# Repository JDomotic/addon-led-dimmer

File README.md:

# 9 Channel PWM Dimmer Addon
This is a custom made PWM dimmer addon which fits on the back of the [Wireless sensor board](https://github.com/JDomotic/esp12-wireless-sensor-board) .

The board can receive commands over uart with configurable transition speed per channel

## Version 1 | 05-01-2019
**Features**:
* Onboard 500ma 3.3v power regulator to power itself and the wireless sensor board
* Support for 12v led strips 
* 9 PWM channels 8 bit

**Schematic**

**BOM**

**Ref**|**Qnty**|**Value**|**Footprint**|**Vendor (LCSC)**
:-----: | :-----: | :-----: | :-----: | :-----:
C1,|1|680uF|Capacitor\_THT:CP\_Radial\_D8.0mm\_P3.50mm|C59427|$0,0906
C2,|1|120uF|Capacitor\_THT:CP\_Radial\_D6.3mm\_P2.50mm|C251018|$0,1182
C7,|1|0.1uf|Capacitor\_SMD:C\_1206\_3216Metric\_Pad1.42x1.75mm\_HandSolder|C128353|$0,0179
D1,|1|1N5817|Diode\_THT:D\_DO-41\_SOD81\_P10.16mm\_Horizontal|C169165|$0,0223
J1,|1|RGB\_VIN|TerminalBlock\_Phoenix:TerminalBlock\_Phoenix\_MKDS-1,5-2\_1x02\_P5.00mm\_Horizontal|C8269|$0,0954
J3,|1|Conn\_01x05\_Male RIGHT|Connector\_PinHeader\_2.54mm:PinHeader\_1x05\_P2.54mm\_Vertical|-|0
J4,|1|Conn\_01x05\_Male|Connector\_PinHeader\_2.54mm:PinHeader\_1x05\_P2.54mm\_Vertical|-|0
J5,|2|RGB\_strip\_3|TerminalBlock\_Phoenix:TerminalBlock\_Phoenix\_MKDS-1,5-4\_1x04\_P5.00mm\_Horizontal|C8269|$0,1908
J6,|2|RGB\_strip\_1|TerminalBlock\_Phoenix:TerminalBlock\_Phoenix\_MKDS-1,5-4\_1x04\_P5.00mm\_Horizontal|C8269|$0,1908
J9,|2|RGB\_strip\_2|TerminalBlock\_Phoenix:TerminalBlock\_Phoenix\_MKDS-1,5-4\_1x04\_P5.00mm\_Horizontal|C8269|$0,1908
L1,|1|100uH|Inductor\_SMD:L\_6.3x6.3\_H3|C10122|$0,0731
Q1, Q2, Q3, Q4, Q5, Q6, Q10, Q11, Q12,|9|PMV16XNR|Package\_TO\_SOT\_SMD:SOT-23|C110920|$0,8064
R1,|1|10K|Resistor\_SMD:R\_0805\_2012Metric\_Pad1.15x1.40mm\_HandSolder|C103904|$0,0025
R2, R3, R4, R5, R6, R7, R8, R9, R10,|9|1K|Resistor\_SMD:R\_0805\_2012Metric\_Pad1.15x1.40mm\_HandSolder|C95781|$0,0360
U1,|1|ATTINY414|Package\_SO:SOIC-14\_3.9x8.7mm\_P1.27mm|C189365|$0,7137
U2,|1|LM2594M-3.3|Package\_SO:SOIC-8\_3.9x4.9mm\_P1.27mm|C316691|$0,6088

**Render**

**Assembled**

**Issues**

As vissible in the assembly, there are a few issues. 
1. The wrong SOT-23 footprint is used. Due this, the mosfets needs to be soldered upside down (This because pin 1 and 2 are flipped) 
2. The wrong pin layout for U2 is used. The trace to pad 1, 2 and 4 needs to be scratched. Pad 4 needs to be connected to D1, pad 8 to 3.3v and pad 7 to VIN.

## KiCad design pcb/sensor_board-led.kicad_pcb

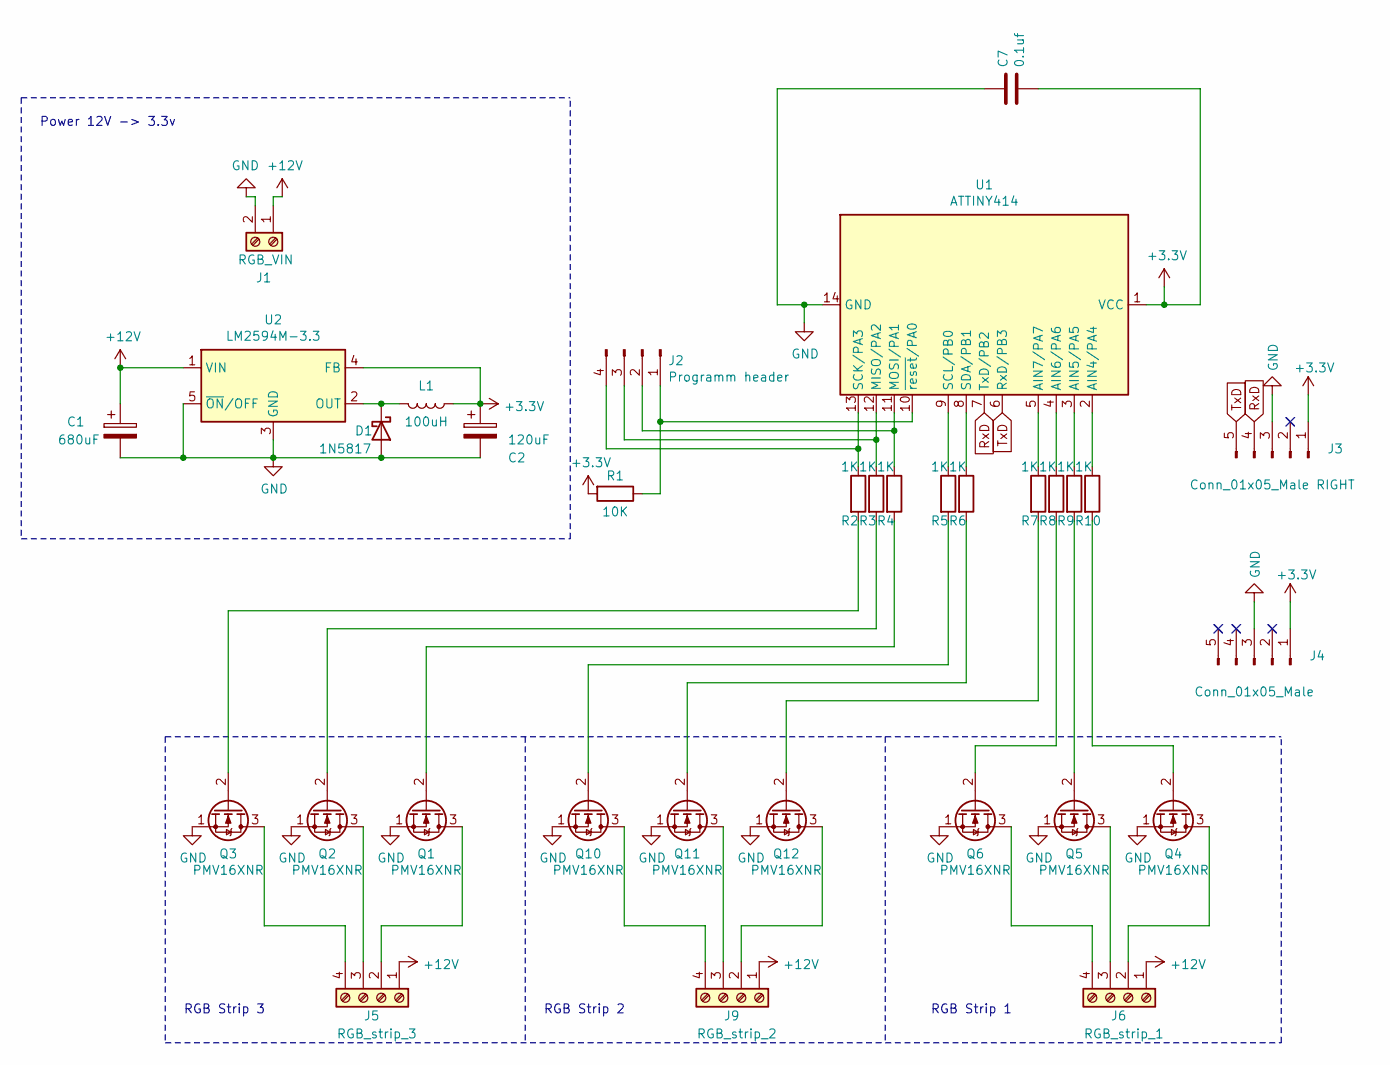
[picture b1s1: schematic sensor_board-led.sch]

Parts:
C1: 680uF; CP_Radial_D8.0mm_P3.50mm
C2: 120uF; CP_Radial_D6.3mm_P2.50mm
C7: 0.1uf; C_1206_3216Metric_Pad1.42x1.75mm_HandSolder
D1: 1N5817; D_DO-41_SOD81_P10.16mm_Horizontal
J1: RGB_VIN; TerminalBlock_Phoenix_MKDS-1,5-2_1x02_P5.00mm_Horizontal
J2: Programm header; PinHeader_1x04_P2.54mm_Vertical_SMD_Pin1Left
J3: Conn_01x05_Male RIGHT; PinHeader_1x05_P2.54mm_Vertical
J4: Conn_01x05_Male; PinHeader_1x05_P2.54mm_Vertical
J5: RGB_strip_3; TerminalBlock_Phoenix_MKDS-1,5-4_1x04_P5.00mm_Horizontal
J6: RGB_strip_1; TerminalBlock_Phoenix_MKDS-1,5-4_1x04_P5.00mm_Horizontal
J9: RGB_strip_2; TerminalBlock_Phoenix_MKDS-1,5-4_1x04_P5.00mm_Horizontal
L1: 100uH; L_6.3x6.3_H3
Q1, Q2, Q3, Q4, Q5, Q6, Q10, Q11, Q12: PMV16XNR; SOT-23
R1: 10K; R_0805_2012Metric_Pad1.15x1.40mm_HandSolder
R2, R3, R4, R5, R6, R7, R8, R9, R10: 1K; R_0805_2012Metric_Pad1.15x1.40mm_HandSolder
U1: ATTINY414; SOIC-14_3.9x8.7mm_P1.27mm
U2: LM2594M-3.3; SOIC-8_3.9x4.9mm_P1.27mm

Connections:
+3V3: C2.1, C7.2, J3.1, J4.1, L1.1, R1.2, U1.1 (VCC), U2.4 (FB)
+12V: C1.1, J1.1, J5.1, J6.1, J9.1, U2.1 (VIN)
GND: C1.2, C2.2, C7.1, D1.2 (A), J1.2, J3.3, J4.3, Q1.1 (S), Q2.1 (S), Q3.1 (S), Q4.1 (S), Q5.1 (S), Q6.1 (S), Q10.1 (S), Q11.1 (S), Q12.1 (S), U1.14 (GND), U2.3 (GND), U2.5 (~ON~/OFF)
unnamed: D1.1 (K), L1.2, U2.2 (OUT)
unnamed: J2.1, R1.1, U1.10 (~reset~/PA0)
unnamed: J2.2, R4.1, U1.11 (MOSI/PA1)
unnamed: J2.3, R3.1, U1.12 (MISO/PA2)
unnamed: J2.4, R2.1, U1.13 (SCK/PA3)
unnamed: J5.2, Q1.3 (D)
unnamed: J5.3, Q2.3 (D)
unnamed: J5.4, Q3.3 (D)
unnamed: J6.2, Q4.3 (D)
unnamed: J6.3, Q5.3 (D)
unnamed: J6.4, Q6.3 (D)
unnamed: J9.2, Q12.3 (D)
unnamed: J9.3, Q11.3 (D)
unnamed: J9.4, Q10.3 (D)
unnamed: Q1.2 (G), R4.2
unnamed: Q2.2 (G), R3.2
unnamed: Q3.2 (G), R2.2
unnamed: Q4.2 (G), R10.2
unnamed: Q5.2 (G), R9.2
unnamed: Q6.2 (G), R8.2
unnamed: Q10.2 (G), R5.2
unnamed: Q11.2 (G), R6.2
unnamed: Q12.2 (G), R7.2
unnamed: R5.1, U1.9 (SCL/PB0)
unnamed: R6.1, U1.8 (SDA/PB1)
unnamed: R7.1, U1.5 (AIN7/PA7)
unnamed: R8.1, U1.4 (AIN6/PA6)
unnamed: R9.1, U1.3 (AIN5/PA5)
unnamed: R10.1, U1.2 (AIN4/PA4)
RxD: J3.4, U1.7 (TxD/PB2)
TxD: J3.5, U1.6 (RxD/PB3)

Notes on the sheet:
Power 12V -> 3.3v
RGB Strip 1
RGB Strip 3
RGB Strip 2

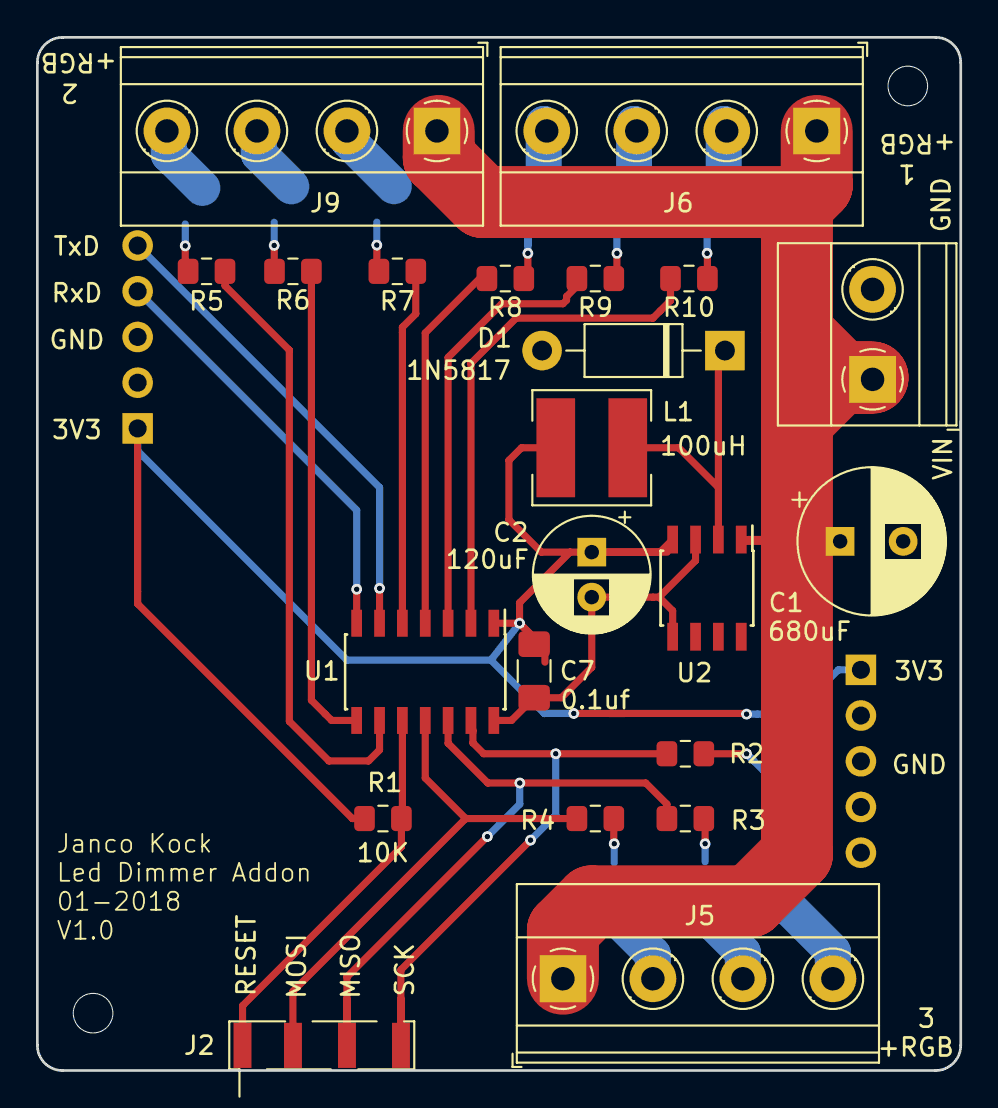
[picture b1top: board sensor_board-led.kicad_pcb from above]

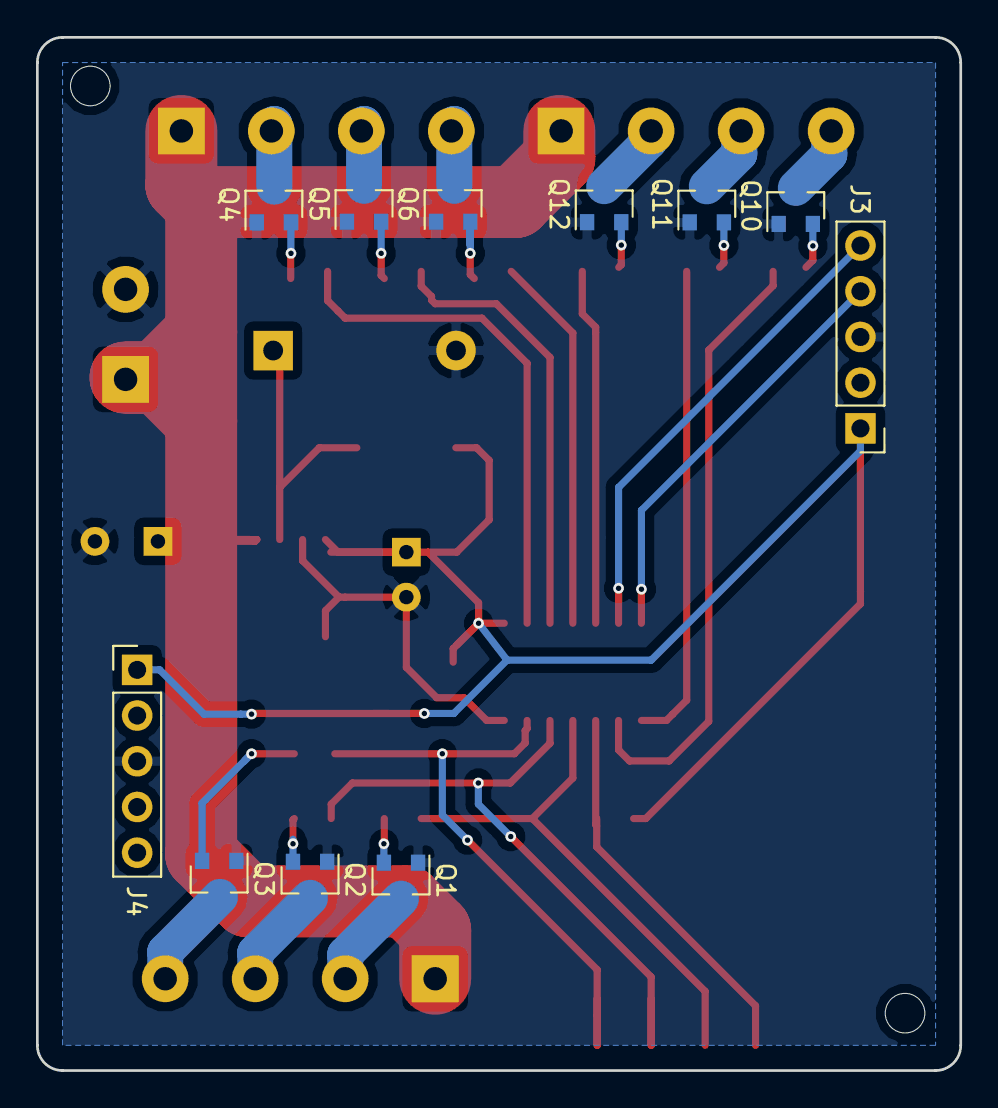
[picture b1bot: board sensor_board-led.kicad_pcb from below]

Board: 2 copper layers, 51.3 x 57.4 mm, 34 parts (11 on the bottom side), 34 nets.

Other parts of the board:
wREF**: MountingHole_2.2mm_M2_DIN965

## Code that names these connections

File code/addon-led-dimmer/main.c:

/*
 * main.c
 *
 * Created: 20-1-2019 15:04:12
 * Author : Janco Kock
 */				
#define F_CPU 10000000UL
#define BAUD_RATE 115200
#define USART0_BAUD_RATE ((float)F_CPU * 64) / (16 * (float)BAUD_RATE)

#define LED_OUTPUT_SCALE 10000UL

#define IDENTIFIER 'O'

#include <avr/io.h>
#include <avr/interrupt.h>
#include <stdbool.h>
#include <string.h>
#include <stdio.h>

// UART methods
int8_t USART_init();
uint8_t USART_read();
void USART_write(const uint8_t data);
void printString(const char myString[]);

const uint8_t gamme8[256] = {
	128, 128, 128, 128, 128, 128, 128, 128, 128, 128, 128, 128, 128, 128, 128, 128, 128, 128, 128, 128,
	129, 129, 129, 129, 129, 129, 129, 129, 129, 129, 129, 129, 129, 129, 129, 129, 129, 129, 129, 129,
	130, 130, 130, 130, 130, 130, 130, 130, 130, 130, 130, 130, 130, 130, 130, 130, 130, 130, 130, 130,
	131, 131, 131, 131, 131, 131, 131, 131, 131, 131, 131, 131, 131, 131, 131, 131, 131, 131, 131, 131,
	132, 132, 132, 132, 132, 132, 132, 132, 132, 132, 132, 132, 132, 132, 132, 132, 132, 132, 132, 132,
	133, 133, 133, 133, 133, 133, 133, 133, 133, 133, 134, 134, 134, 134, 134, 134, 134, 134, 134, 134,
	135, 135, 135, 135, 135, 135, 135, 135, 135, 135, 136, 136, 136, 136, 136, 136, 136, 136, 136, 136,
	137, 137, 137, 137, 137, 137, 137, 137, 137, 137, 138, 138, 138, 138, 138, 138, 138, 138, 138, 138,
	139, 139, 139, 139, 139, 139, 140, 140, 140, 140, 140, 140, 141, 141, 141, 141, 141, 141, 141, 141,
	142, 142, 142, 142, 143, 143, 143, 143, 143, 144, 144, 144, 144, 144, 145, 145, 145, 145, 145, 145,
	146, 146, 146, 147, 147, 147, 148, 148, 148, 149, 149, 149, 150, 150, 150, 151, 151, 151, 152, 152,
	152, 153, 153, 153, 154, 154, 154, 155, 155, 155, 156, 156, 156, 157, 157, 158, 158, 159, 159, 160,
	160, 161, 162, 163, 164, 165, 166, 167, 168, 169, 170, 171, 172, 173, 174, 175
};

typedef struct tick_value {uint8_t tick; uint8_t LEDS_PORTA; uint8_t LEDS_PORTB;} tick_value;
tick_value port_output_values_0[10] = {0};
tick_value port_output_values_1[10] = {0};
tick_value *port_output_values = port_output_values_0;
uint8_t current_port_values = 0;

uint8_t port_output_value_index = 0;
uint8_t current_tick = 0;

uint8_t wanted_led_output_values[18];
long led_output_values[9] = {0};
	
uint8_t uart_led_channel = 0;
bool recalculate_port_output_values = false;

///
/// Timer A for software PWM
///
ISR(TCA0_OVF_vect){
	current_tick++;

	//Set top based on gamma correction 
	TCA0_SINGLE_PER = gamme8[current_tick];
	
	if(current_tick == 0){
		port_output_value_index = 0;
		// Set correct output buffer
		if(current_port_values == 0){
			port_output_values = port_output_values_0;
		}else{
			port_output_values = port_output_values_1;
		}
	}
	
	if(current_tick == port_output_values[port_output_value_index].tick){
		PORTA_OUT = port_output_values[port_output_value_index].LEDS_PORTA; 
		PORTB_OUT = port_output_values[port_output_value_index].LEDS_PORTB;
		++port_output_value_index; 
	}

	// Clear interrupt flag
	TCA0_SINGLE_INTFLAGS = 0b00000001; 
} 

///
/// Timer B for UART package timeout check
///
ISR(TCB0_INT_vect){
	// Timeout between UART package occurs. Reset channel
	uart_led_channel = 0;
	// Disable
	TCB0_CTRLA = 0b00000010;
	// Clear interrupt flag
	TCB0_INTFLAGS = 0b00000001;
	// Write 'out of sync' package
	USART_write(IDENTIFIER);
}

///
/// UART methods
///
ISR(USART0_RXC_vect){
	wanted_led_output_values[uart_led_channel] =  USART0.RXDATAL;
	
	// Update package is done, so reset the UART package channel to 0
	if(uart_led_channel == 17){
		uart_led_channel = 0;
		
		recalculate_port_output_values = true;
		
		// Disable package timeout timer
		TCB0.CNT = 0;
		TCB0_CTRLA = 0b00000010;
	} else{
		uart_led_channel++;
		
		// Enable package timeout timer.
		TCB0.CNT = 0;
		TCB0_CTRLA = 0b00000011;
	}
}

int8_t USART_init(){
	int8_t sigrow_val = SIGROW.OSC20ERR3V; // read signed error
	int32_t baud_reg_val = USART0_BAUD_RATE;
	baud_reg_val *= (1024 + sigrow_val); // sum resolution + error
	baud_reg_val /= 1024; // divide by resolution
	USART0.BAUD = (int16_t) baud_reg_val;
	
	// Enable receive interrupt 
	USART0.CTRLA = 0b10000000;
  
	USART0.CTRLB = 0 << USART_MPCM_bp       /* Multi-processor Communication Mode: disabled */
	| 0 << USART_ODME_bp     /* Open Drain Mode Enable: disabled */
	| 1 << USART_RXEN_bp     /* Receiver enable: enabled */
	| USART_RXMODE_NORMAL_gc /* Normal mode */
	| 0 << USART_SFDEN_bp    /* Start Frame Detection Enable: disabled */
	| 1 << USART_TXEN_bp;    /* Transmitter Enable: enabled */

	USART0.CTRLC = USART_CMODE_ASYNCHRONOUS_gc /* Asynchronous Mode */
	| USART_CHSIZE_8BIT_gc /* Character size: 8 bit */
	| USART_PMODE_DISABLED_gc /* No Parity */
	| USART_SBMODE_1BIT_gc; /* 1 stop bit */

	return 0;
}

uint8_t USART_read()
{
	while (!(USART0.STATUS & USART_RXCIF_bm));
	return USART0.RXDATAL;
}

void USART_write(const uint8_t data)
{
	while (!(USART0.STATUS & USART_DREIF_bm));
	USART0.TXDATAL = data;
}

void printString(const char myString[]) {
	uint8_t i = 0;
	while (myString[i]) {
		USART_write(myString[i]);
		i++;
	}
}


void calculate_steps(){
	uint8_t tmp;
	uint8_t steps[10];
	uint8_t output_values[9];
	
	tick_value *tmp_output;
	if(current_port_values == 0){
		tmp_output = port_output_values_1;
	}else{
		tmp_output = port_output_values_0;
	}
	
	// Copy led output values and convert them to uint8		
	steps[0] = 0;
	for(uint8_t i = 1; i < 10; i++){
		output_values[i-1] = ((led_output_values[i-1]) / LED_OUTPUT_SCALE);
		steps[i] = output_values[i-1];
	}
	
	// Sort steps
	uint8_t *steps_offset = &steps[1];
	for(uint8_t i = 0; i < 9; i++){
		for(uint8_t j = 0; j < (9-i-1); j++){
			if (steps_offset[j] > steps_offset[j + 1]){
				tmp = steps_offset[j];
				steps_offset[j] = steps_offset[j + 1];
				steps_offset[j + 1] = tmp;
			}
		}
	}
	
	tmp_output[0].tick = 0;
	tmp_output[0].LEDS_PORTB =	((output_values[1] > 0) << 1) | (output_values[2] > 0);
	tmp_output[0].LEDS_PORTA =	((output_values[0] > 0) << 7) |
								((output_values[5] > 0) << 6) | ((output_values[4] > 0) << 5) | ((output_values[3] > 0) << 4) |
								((output_values[8] > 0) << 3) | ((output_values[7] > 0) << 2) | ((output_values[6] > 0) << 1);
	
	uint8_t index = 0;

	for(uint8_t i = 1; i < 10; i++){
		// Skip if step is the same as previous one
		if(steps[i] != steps[i - 1]){
			index++;
			tmp_output[index].tick = steps[i];
			tmp_output[index].LEDS_PORTB =	((output_values[1] > steps[i]) << 1) | (output_values[2] > steps[i]);
			tmp_output[index].LEDS_PORTA =	((output_values[0] > steps[i]) << 7) |
											((output_values[5] > steps[i]) << 6) | ((output_values[4] > steps[i]) << 5) | ((output_values[3] > steps[i]) << 4) |
											((output_values[8] > steps[i]) << 3) | ((output_values[7] > steps[i]) << 2) | ((output_values[6] > steps[i]) << 1);
		}
	}
	
	// Set other values back to zero
	for(++index; index < 10; index++){
		tmp_output[index].tick = 0;
	}
	
	// Switch output buffer
	current_port_values = !current_port_values;
}


int main(void)
{
	///
	/// CPU clock settings
	///
	
	// Disable change protection
	CPU_CCP = 0xD8;
	
	// Set main pre-scaler division to 2 (so 20mhz / 2 = 10mhz)
	CLKCTRL_MCLKCTRLB = 0b00000001;
	
	// Lock the registers again
	CLKCTRL_MCLKLOCK = 1;
	
	// Set TX pin high
	PORTB_OUT = 0b00000100;
	
	// PB0 and PB1 output, RX and TX as output
	PORTB_DIR = 0b00000111;
	// PA1 - PA7 output
	PORTA_DIR = 0b11111110;
	
	USART_init();	
	
	///
	/// Timer A for software PWM
	///
	
	// Timer A top 128
	TCA0_SINGLE_PER = 128; 
	// Enable timer A and set division to 2
	TCA0_SINGLE_CTRLA = 0b00000001;
	// Enable overflow interrupt
	TCA0_SINGLE_INTCTRL = 0b00000001; 
	
	///
	/// Timer B for UART package timeout check
	///
	
	// Set tcb0 top
	TCB0.CCMP = 0xffff;
	// Set to timeout check mode
	TCB0_CTRLB = 0b00000000;
	// Enable interrupt
	TCB0.INTCTRL = 0b00000001;
	
	// Enable all interrupt
	sei();
	
	uint8_t i;
	uint8_t fade_channel;
	
	long led_output_fade_steps_values[9] = {0};
	int led_output_fade_steps[9] = {0};
	bool need_to_recalculate = false;
	
	while(1){
		if(recalculate_port_output_values){
			recalculate_port_output_values = false;
			
			// Calculate the fade steps
			fade_channel = 8;
			for(i = 0; i < 9; i++){
				fade_channel++;
				
				long scaled_value = (wanted_led_output_values[i] * LED_OUTPUT_SCALE);
				long step_value =  (scaled_value - led_output_values[i]) /  (wanted_led_output_values[fade_channel] * 4);
				
				led_output_fade_steps_values[i] = step_value;
				
				led_output_fade_steps[i] = (wanted_led_output_values[fade_channel]*4);
			}
			continue;
		}
		need_to_recalculate = false;
		for(i = 0; i < 9; i++){
			if(led_output_fade_steps[i] != 0){
				led_output_fade_steps[i]--;
				led_output_values[i] += led_output_fade_steps_values[i];
				need_to_recalculate = true;
			}
		}
		if(need_to_recalculate)
			calculate_steps();
		continue;
	}
}

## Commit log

2021-01-15 Init
2021-01-15 New code
2021-01-16 Repository cleanup
2021-01-16 Add readme Renamed kicad files
2021-03-24 Implement I2C
2021-04-07 Change interface to I2C
    Repo cleanup
2024-02-18 Upgrade PCB project to KiCad 6 and bundle the ATtiny1614 symbol
